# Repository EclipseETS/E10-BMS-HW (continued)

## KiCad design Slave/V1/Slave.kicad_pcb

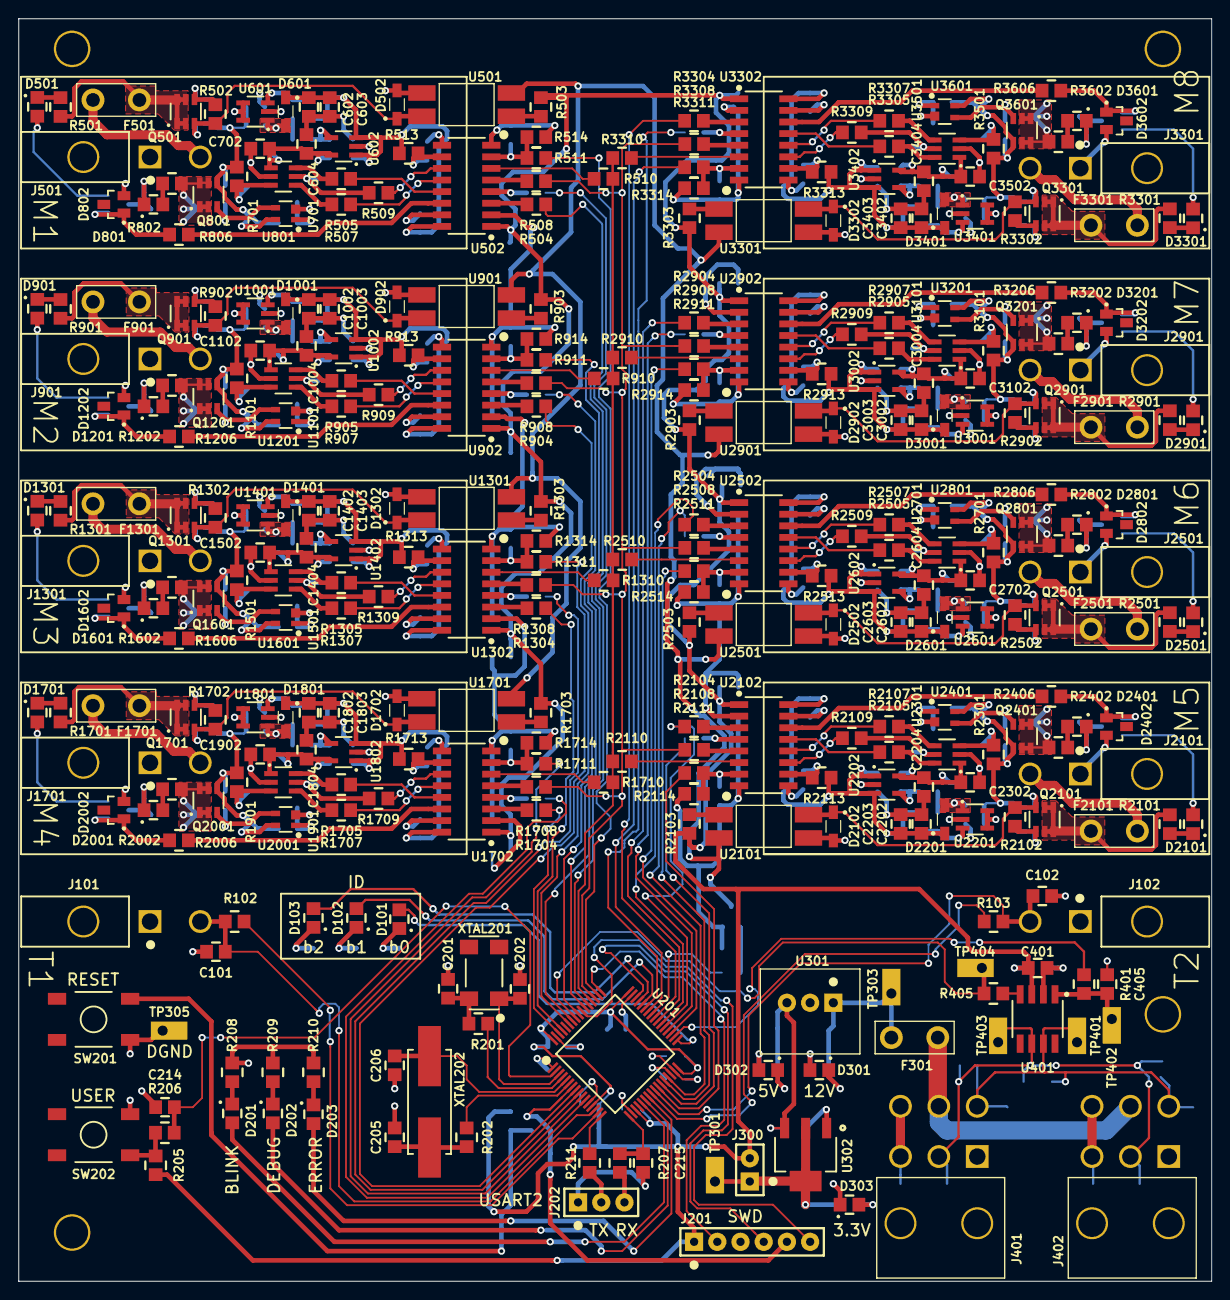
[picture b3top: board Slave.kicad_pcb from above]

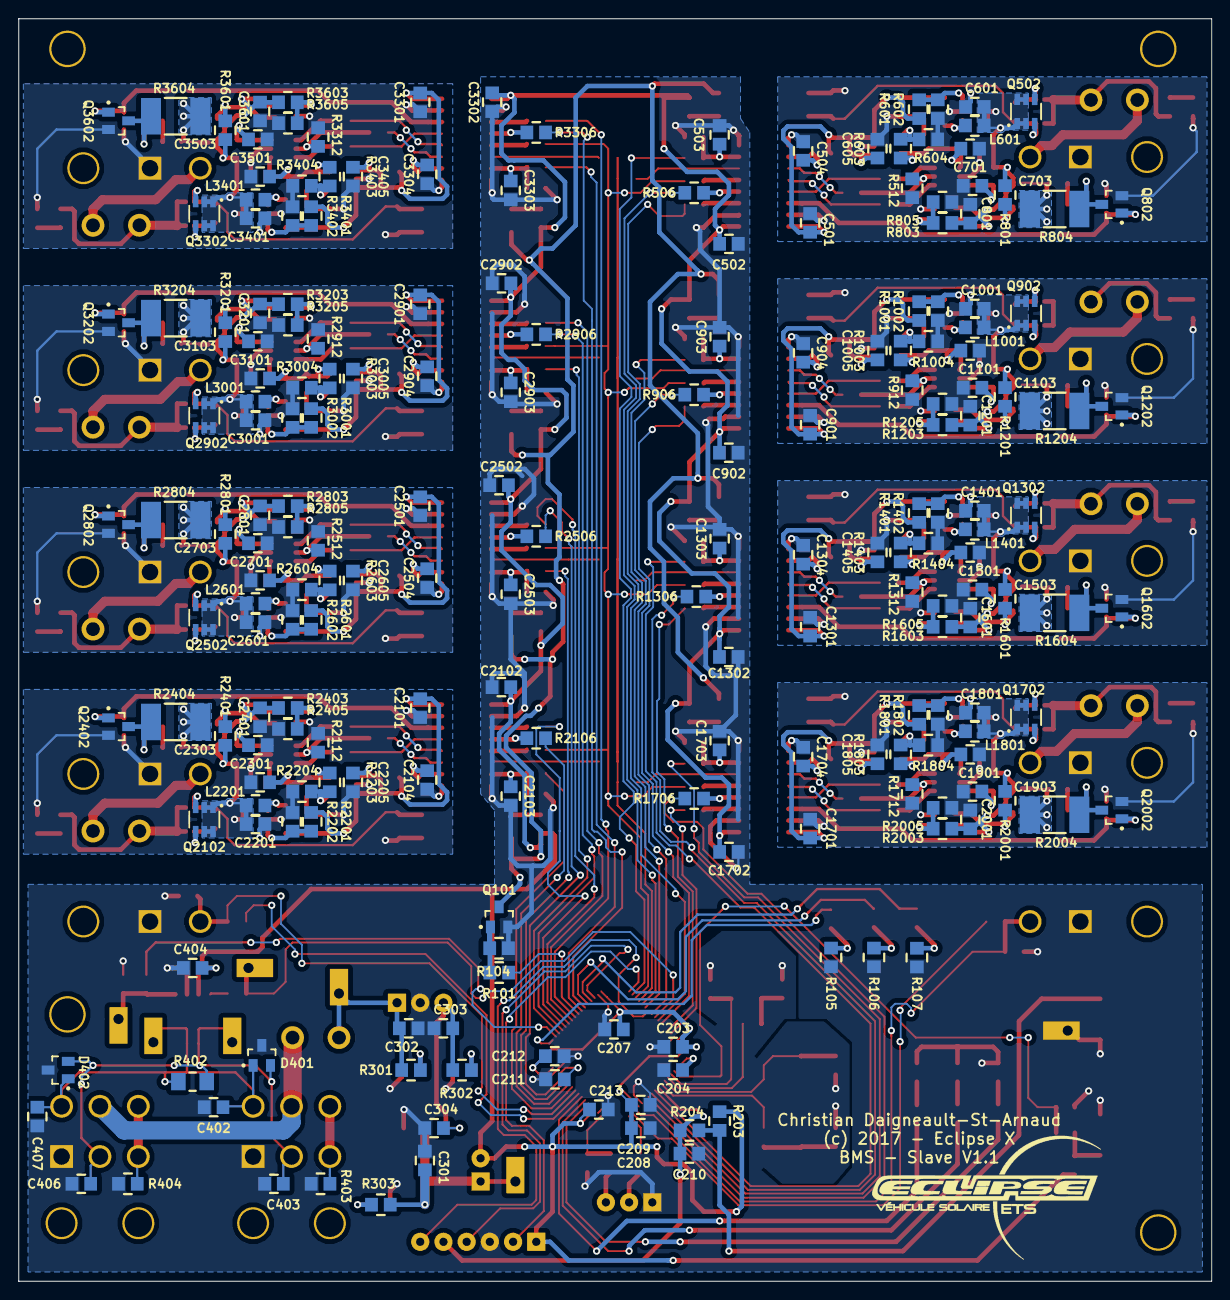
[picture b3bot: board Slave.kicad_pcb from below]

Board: 2 copper layers, 130.6 x 138.2 mm, 537 parts (210 on the bottom side), 345 nets.

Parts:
C101, C102, C204, C208, C401, C701, C1101, C1501, C1901, C2301, C2701, C3101, C3501: 885012107015; C0805
C201, C202: 885012007027; C0805
C203, C207, C210, C212, C213, C214, C404, C501, C502, C504, C702, C801, C901, C902, C904, C1102, C1201, C1301, C1302, C1304, C1502, C1601, C1701, C1702, C1704, C1902, C2001, C2101, C2102, C2104, C2302, C2401, C2501, C2502, C2504, C2702, C2801, C2901, C2902, C2904, C3102, C3201, C3301, C3302, C3304, C3502, C3601: 885012207098; C0805
C205, C206, C215, C402, C403, C406, C407: 885012007053; C0805
C209: 885012207092; C0805
C211, C302, C303: 885012107018; C0805
C301: 885012107005; C0805
C304, C601, C602, C603, C604, C605, C1001, C1002, C1003, C1004, C1005, C1401, C1402, C1403, C1404, C1405, C1801, C1802, C1803, C1804, C1805, C2201, C2202, C2203, C2204, C2205, C2601, C2602, C2603, C2604, C2605, C3001, C3002, C3003, C3004, C3005, C3401, C3402, C3403, C3404, C3405: 885012107014; C0805
C405, C503, C903, C1303, C1703, C2103, C2503, C2903, C3303: 885012207080; C0805
C703, C1103, C1503, C1903, C2303, C2703, C3103, C3503: 885012207047; C0805
D101, D102, D103, D201, D301, D302, D303, D801, D1201, D1601, D2001, D2401, D2801, D3201, D3601: 150080VS75000; LED_0805_GREEN
D202: 150080YS75000; LED_0805_YELLOW
D203, D501, D901, D1301, D1701, D2101, D2501, D2901, D3301: 150080RS75000; LED_0805_RED
D401, D402: D1213A-02SOL-7; SOT-23-3
D502, D601, D902, D1001, D1302, D1401, D1702, D1801, D2102, D2201, D2502, D2601, D2902, D3001, D3302, D3401: NSR0530HT1G; SOD-323
D802, D1202, D1602, D2002, D2402, D2802, D3202, D3602: MMBZ12VALT1G; SOT-23-3
F301, F501, F901, F1301, F1701, F2101, F2501, F2901, F3301: 39511000440; TE5_395
J101, J102, J501, J901, J1301, J1701, J2101, J2501, J2901, J3301: 649002227222
J201: Header_Male_Pin_2.54mm_1X6_,_Unshrouded; Headers_2.54mm_1X6
J202: Header_Male_Pin_2.54mm_1X3_,_Unshrouded; Headers_2.54mm_1X3
J300: Header_Male_Pin_2.54mm_1X2_,_Unshrouded; Headers_2.54mm_1X2
J401, J402: 649006227222
L601, L1001, L1401, L1801, L2201, L2601, L3001, L3401: MLZ2012N101LT000; I0805
Q101: 2N7002P,215; SOT-23-3
Q501, Q502, Q801, Q901, Q902, Q1201, Q1301, Q1302, Q1601, Q1701, Q1702, Q2001, Q2101, Q2102, Q2401, Q2501, Q2502, Q2801, Q2901, Q2902, Q3201, Q3301, Q3302, Q3601: CPH6347-TL-W; TSOT-23-6
Q802, Q1202, Q1602, Q2002, Q2402, Q2802, Q3202, Q3602: BSS806NH6327XTSA1; SOT-23-3
R101, R105, R106, R107, R208, R209, R210, R303: RC0805JR-07470RL; R0805
R102, R103: RC0805JR-0733KL; R0805
R104, R203, R205, R207, R301, R510, R511, R512, R513, R603, R910, R911, R912, R913, R1003, R1310, R1311, R1312, R1313, R1403, R1710, R1711, R1712, R1713, R1803, R2110, R2111, R2112, R2113, R2203, R2510, R2511, R2512, R2513, R2603, R2910, R2911, R2912, R2913, R3003, R3310, R3311, R3312, R3313, R3403: RC0805JR-074K7L; R0805
R201, R202, R403, R404: RC0805JR-070RL; R0805
R204, R206, R401, R405, R504, R505, R506, R507, R508, R509, R701, R904, R905, R906, R907, R908, R909, R1101, R1304, R1305, R1306, R1307, R1308, R1309, R1501, R1704, R1705, R1706, R1707, R1708, R1709, R1901, R2104, R2105, R2106, R2107, R2108, R2109, R2301, R2504, R2505, R2506, R2507, R2508, R2509, R2701, R2904, R2905, R2906, R2907, R2908, R2909, R3101, R3304, R3305, R3306, R3307, R3308, R3309, R3501: RC0805JR-07100RL; R0805
R211, R302, R501, R802, R901, R1202, R1301, R1602, R1701, R2002, R2101, R2402, R2501, R2802, R2901, R3202, R3301, R3602: RC0805JR-071KL; R0805
R402: RC1206JR-07120RL; R1206
R502, R514, R801, R902, R914, R1201, R1302, R1314, R1601, R1702, R1714, R2001, R2102, R2114, R2401, R2502, R2514, R2801, R2902, R2914, R3201, R3302, R3314, R3601: RC0805JR-07470KL; R0805
R503, R903, R1303, R1703, R2103, R2503, R2903, R3303: RC0805JR-07330RL; R0805
R601, R1001, R1401, R1801, R2201, R2601, R3001, R3401: RC0805JR-071ML; R0805
R602, R1002, R1402, R1802, R2202, R2602, R3002, R3402: RC0805FR-07324KL; R0805
R604, R1004, R1404, R1804, R2204, R2604, R3004, R3404: RC0805FR-0712K1L; R0805
R803, R1203, R1603, R2003, R2403, R2803, R3203, R3603: RC0805JR-07560KL; R0805
R804, R1204, R1604, R2004, R2404, R2804, R3204, R3604: 352210RJT; R2512
R805, R1205, R1605, R2005, R2405, R2805, R3205, R3605: RC0805JR-07100KL; R0805
R806, R1206, R1606, R2006, R2406, R2806, R3206, R3606: RC0805JR-076K8L; R0805
SW201, SW202: PTS645SM43SMTR92; PTS645_6X6X4_SMD
TP301, TP303, TP305, TP401, TP402, TP403, TP404: Test_Point_THM; Keystone_5001
U201: STM32F446RE; LQFP-64
U301: OKI-78SR-5/1.5-W36-C; OKI-78SR_Vertical
U302: AZ1117IH-3.3TRG1; SOT-223-3
U401: SN65HVD232DR; SOIC-8
U501, U901, U1301, U1701, U2101, U2501, U2901, U3301: LTV-816S; 4-SMD
U502, U902, U1302, U1702, U2102, U2502, U2902, U3302: SI8641AB-B-IS1; SOIC-16
U601, U1001, U1401, U1801, U2201, U2601, U3001, U3401: AP3015KTR-G1; SOT-23-5
U602, U1002, U1402, U1802, U2202, U2602, U3002, U3402: AP2202K-ADJTRG1; SOT-23-5
U701, U1101, U1501, U1901, U2301, U2701, U3101, U3501: ADC121S021CIMF/NOPB; SOT-23-6
U801, U1201, U1601, U2001, U2401, U2801, U3201, U3601: ADCMP350YKSZ-REEL7; SC70-4
XTAL201: ABS25-32.768KHZ-6-T; ABS25
XTAL202: ABLS-8.000MHZ-D-T; HC49_US

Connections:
3.3V: C301.2, J300.1, R303.2, TP301.1, U302.2, U302.4
5V: C303.2, C304.2, R302.2, U301.3, U302.3
12V: C302.2, F301.2, R301.2, TP303.1, U301.1
/BALANCING_PWM_1: R504.2, U201.58
/BALANCING_PWM_2: R904.2, U201.59
/BALANCING_PWM_3: R1304.2, U201.61
/BALANCING_PWM_4: R1704.2, U201.62
/BALANCING_PWM_5: R2104.2, U201.37
/BALANCING_PWM_6: R2504.2, U201.38
/BALANCING_PWM_7: R2904.2, U201.39
/BALANCING_PWM_8: R3304.2, U201.40
/CAN1/CAN_N: C403.2, C406.2, D401.2, D402.2, J401.2, J402.2, R402.2, TP403.1, U401.6
/CAN1/CAN_P: C402.2, C407.2, D401.1, D402.1, J401.4, J402.4, R402.1, TP401.1, U401.7
/CAN1/Shield1: J401.3, J401.6, R403.1
/CAN1/Shield2: J402.3, J402.6, R404.1
/CAN2_RX: R405.1, TP404.1, U201.57
/CAN2_TX: R401.1, U201.34
/CS_1: R506.2, U201.53
/CS_2: R906.2, U201.56
/CS_3: R1306.2, U201.9
/CS_4: R1706.2, U201.11
/CS_5: R2106.2, U201.27
/CS_6: R2506.2, U201.29
/CS_7: R2906.2, U201.36
/CS_8: R3306.2, U201.43
/DATA_ENABLE_1: R511.2, U201.50
/DATA_ENABLE_2: R911.2, U201.54
/DATA_ENABLE_3: R1311.2, U201.8
/DATA_ENABLE_4: R1711.2, U201.10
/DATA_ENABLE_5: R2111.2, U201.26
/DATA_ENABLE_6: R2511.2, U201.28
/DATA_ENABLE_7: R2911.2, U201.35
/DATA_ENABLE_8: R3311.2, U201.42
/ID_0: D101.2, U201.33
/ID_1: D102.2, U201.44
/ID_2: D103.2, U201.45
/MISO: R510.2, R910.2, R1310.2, R1710.2, R2110.2, R2510.2, R2910.2, R3310.2, U201.52
/Module 1/+VREF: C604.2, C701.1, C702.1, R603.2, U602.5, U701.1
/Module 1/BALANCE_PWM: R806.1, U502.14
/Module 1/BVDD: C501.2, C602.2, C603.2, C605.2, D601.1, R513.2, R601.2, U502.16, U602.1, U602.3
/Module 1/Balancing/Drain_P_Mosfet: Q801.1, Q801.2, Q801.5, Q801.6, R802.1, R804.2
/Module 1/CELL+: F501.2, Q501.1, Q501.2, Q501.5, Q501.6, R501.2
/Module 1/CELL-: C501.1, C504.1, C601.1, C602.1, C603.1, C604.1, C605.1, C701.2, C702.2, C703.1, C801.2, D501.2, D502.2, D802.2, J501.1, Q802.2, R512.1, R602.1, R604.1, R805.1, U501.3, U502.9, U502.15, U601.2, U602.2, U701.2, U801.2
/Module 1/CELL_Voltage: C601.2, C801.1, L601.1, Q502.1, Q502.2, Q502.5, Q502.6, Q801.4, R701.1, R801.1, R803.2, U601.4, U601.5, U801.4
/Module 1/CS: R505.2, U502.13
/Module 1/Power Supply Front End/SW: D601.2, L601.2, U601.1
/Module 1/SCLK: R507.2, U502.12
/Module 1/SDATA: R509.2, U502.11
/Module 1/Voltage Reading/CS: R505.1, U701.6
/Module 1/Voltage Reading/SCLK: R507.1, U701.4
/Module 1/Voltage Reading/SDATA: R509.1, R512.2, U701.5
/Module 2/+VREF: C1004.2, C1101.1, C1102.1, R1003.2, U1002.5, U1101.1
/Module 2/BALANCE_PWM: R1206.1, U902.14
/Module 2/BVDD: C901.2, C1002.2, C1003.2, C1005.2, D1001.1, R913.2, R1001.2, U902.16, U1002.1, U1002.3
/Module 2/Balancing/Drain_P_Mosfet: Q1201.1, Q1201.2, Q1201.5, Q1201.6, R1202.1, R1204.2
/Module 2/CELL+: F901.2, Q901.1, Q901.2, Q901.5, Q901.6, R901.2
/Module 2/CELL-: C901.1, C904.1, C1001.1, C1002.1, C1003.1, C1004.1, C1005.1, C1101.2, C1102.2, C1103.1, C1201.2, D901.2, D902.2, D1202.2, J901.1, Q1202.2, R912.1, R1002.1, R1004.1, R1205.1, U901.3, U902.9, U902.15, U1001.2, U1002.2, U1101.2, U1201.2
/Module 2/CELL_Voltage: C1001.2, C1201.1, L1001.1, Q902.1, Q902.2, Q902.5, Q902.6, Q1201.4, R1101.1, R1201.1, R1203.2, U1001.4, U1001.5, U1201.4
/Module 2/CS: R905.2, U902.13
/Module 2/Power Supply Front End/SW: D1001.2, L1001.2, U1001.1
/Module 2/SCLK: R907.2, U902.12
/Module 2/SDATA: R909.2, U902.11
/Module 2/Voltage Reading/CS: R905.1, U1101.6
/Module 2/Voltage Reading/SCLK: R907.1, U1101.4
/Module 2/Voltage Reading/SDATA: R909.1, R912.2, U1101.5
/Module 3/+VREF: C1404.2, C1501.1, C1502.1, R1403.2, U1402.5, U1501.1
/Module 3/BALANCE_PWM: R1606.1, U1302.14
/Module 3/BVDD: C1301.2, C1402.2, C1403.2, C1405.2, D1401.1, R1313.2, R1401.2, U1302.16, U1402.1, U1402.3
/Module 3/Balancing/Drain_P_Mosfet: Q1601.1, Q1601.2, Q1601.5, Q1601.6, R1602.1, R1604.2
/Module 3/CELL+: F1301.2, Q1301.1, Q1301.2, Q1301.5, Q1301.6, R1301.2
/Module 3/CELL-: C1301.1, C1304.1, C1401.1, C1402.1, C1403.1, C1404.1, C1405.1, C1501.2, C1502.2, C1503.1, C1601.2, D1301.2, D1302.2, D1602.2, J1301.1, Q1602.2, R1312.1, R1402.1, R1404.1, R1605.1, U1301.3, U1302.9, U1302.15, U1401.2, U1402.2, U1501.2, U1601.2
/Module 3/CELL_Voltage: C1401.2, C1601.1, L1401.1, Q1302.1, Q1302.2, Q1302.5, Q1302.6, Q1601.4, R1501.1, R1601.1, R1603.2, U1401.4, U1401.5, U1601.4
/Module 3/CS: R1305.2, U1302.13
/Module 3/Power Supply Front End/SW: D1401.2, L1401.2, U1401.1
/Module 3/SCLK: R1307.2, U1302.12
/Module 3/SDATA: R1309.2, U1302.11
/Module 3/Voltage Reading/CS: R1305.1, U1501.6
/Module 3/Voltage Reading/SCLK: R1307.1, U1501.4
/Module 3/Voltage Reading/SDATA: R1309.1, R1312.2, U1501.5
/Module 4/+VREF: C1804.2, C1901.1, C1902.1, R1803.2, U1802.5, U1901.1
/Module 4/BALANCE_PWM: R2006.1, U1702.14
/Module 4/BVDD: C1701.2, C1802.2, C1803.2, C1805.2, D1801.1, R1713.2, R1801.2, U1702.16, U1802.1, U1802.3
/Module 4/Balancing/Drain_P_Mosfet: Q2001.1, Q2001.2, Q2001.5, Q2001.6, R2002.1, R2004.2
/Module 4/CELL+: F1701.2, Q1701.1, Q1701.2, Q1701.5, Q1701.6, R1701.2
/Module 4/CELL-: C1701.1, C1704.1, C1801.1, C1802.1, C1803.1, C1804.1, C1805.1, C1901.2, C1902.2, C1903.1, C2001.2, D1701.2, D1702.2, D2002.2, J1701.1, Q2002.2, R1712.1, R1802.1, R1804.1, R2005.1, U1701.3, U1702.9, U1702.15, U1801.2, U1802.2, U1901.2, U2001.2
/Module 4/CELL_Voltage: C1801.2, C2001.1, L1801.1, Q1702.1, Q1702.2, Q1702.5, Q1702.6, Q2001.4, R1901.1, R2001.1, R2003.2, U1801.4, U1801.5, U2001.4
/Module 4/CS: R1705.2, U1702.13
/Module 4/Power Supply Front End/SW: D1801.2, L1801.2, U1801.1
/Module 4/SCLK: R1707.2, U1702.12
/Module 4/SDATA: R1709.2, U1702.11
/Module 4/Voltage Reading/CS: R1705.1, U1901.6
/Module 4/Voltage Reading/SCLK: R1707.1, U1901.4
/Module 4/Voltage Reading/SDATA: R1709.1, R1712.2, U1901.5
/Module 5/+VREF: C2204.2, C2301.1, C2302.1, R2203.2, U2202.5, U2301.1
/Module 5/BALANCE_PWM: R2406.1, U2102.14
/Module 5/BVDD: C2101.2, C2202.2, C2203.2, C2205.2, D2201.1, R2113.2, R2201.2, U2102.16, U2202.1, U2202.3
/Module 5/Balancing/Drain_P_Mosfet: Q2401.1, Q2401.2, Q2401.5, Q2401.6, R2402.1, R2404.2
/Module 5/CELL+: F2101.2, Q2101.1, Q2101.2, Q2101.5, Q2101.6, R2101.2
/Module 5/CELL-: C2101.1, C2104.1, C2201.1, C2202.1, C2203.1, C2204.1, C2205.1, C2301.2, C2302.2, C2303.1, C2401.2, D2101.2, D2102.2, D2402.2, J2101.1, Q2402.2, R2112.1, R2202.1, R2204.1, R2405.1, U2101.3, U2102.9, U2102.15, U2201.2, U2202.2, U2301.2, U2401.2
/Module 5/CELL_Voltage: C2201.2, C2401.1, L2201.1, Q2102.1, Q2102.2, Q2102.5, Q2102.6, Q2401.4, R2301.1, R2401.1, R2403.2, U2201.4, U2201.5, U2401.4
/Module 5/CS: R2105.2, U2102.13
/Module 5/Power Supply Front End/SW: D2201.2, L2201.2, U2201.1
/Module 5/SCLK: R2107.2, U2102.12
/Module 5/SDATA: R2109.2, U2102.11
/Module 5/Voltage Reading/CS: R2105.1, U2301.6
/Module 5/Voltage Reading/SCLK: R2107.1, U2301.4
/Module 5/Voltage Reading/SDATA: R2109.1, R2112.2, U2301.5
/Module 6/+VREF: C2604.2, C2701.1, C2702.1, R2603.2, U2602.5, U2701.1
/Module 6/BALANCE_PWM: R2806.1, U2502.14
/Module 6/BVDD: C2501.2, C2602.2, C2603.2, C2605.2, D2601.1, R2513.2, R2601.2, U2502.16, U2602.1, U2602.3
/Module 6/Balancing/Drain_P_Mosfet: Q2801.1, Q2801.2, Q2801.5, Q2801.6, R2802.1, R2804.2
/Module 6/CELL+: F2501.2, Q2501.1, Q2501.2, Q2501.5, Q2501.6, R2501.2
/Module 6/CELL-: C2501.1, C2504.1, C2601.1, C2602.1, C2603.1, C2604.1, C2605.1, C2701.2, C2702.2, C2703.1, C2801.2, D2501.2, D2502.2, D2802.2, J2501.1, Q2802.2, R2512.1, R2602.1, R2604.1, R2805.1, U2501.3, U2502.9, U2502.15, U2601.2, U2602.2, U2701.2, U2801.2
/Module 6/CELL_Voltage: C2601.2, C2801.1, L2601.1, Q2502.1, Q2502.2, Q2502.5, Q2502.6, Q2801.4, R2701.1, R2801.1, R2803.2, U2601.4, U2601.5, U2801.4
/Module 6/CS: R2505.2, U2502.13
/Module 6/Power Supply Front End/SW: D2601.2, L2601.2, U2601.1
/Module 6/SCLK: R2507.2, U2502.12
/Module 6/SDATA: R2509.2, U2502.11
/Module 6/Voltage Reading/CS: R2505.1, U2701.6
/Module 6/Voltage Reading/SCLK: R2507.1, U2701.4
/Module 6/Voltage Reading/SDATA: R2509.1, R2512.2, U2701.5
/Module 7/+VREF: C3004.2, C3101.1, C3102.1, R3003.2, U3002.5, U3101.1
/Module 7/BALANCE_PWM: R3206.1, U2902.14
/Module 7/BVDD: C2901.2, C3002.2, C3003.2, C3005.2, D3001.1, R2913.2, R3001.2, U2902.16, U3002.1, U3002.3
/Module 7/Balancing/Drain_P_Mosfet: Q3201.1, Q3201.2, Q3201.5, Q3201.6, R3202.1, R3204.2
/Module 7/CELL+: F2901.2, Q2901.1, Q2901.2, Q2901.5, Q2901.6, R2901.2
/Module 7/CELL-: C2901.1, C2904.1, C3001.1, C3002.1, C3003.1, C3004.1, C3005.1, C3101.2, C3102.2, C3103.1, C3201.2, D2901.2, D2902.2, D3202.2, J2901.1, Q3202.2, R2912.1, R3002.1, R3004.1, R3205.1, U2901.3, U2902.9, U2902.15, U3001.2, U3002.2, U3101.2, U3201.2
/Module 7/CELL_Voltage: C3001.2, C3201.1, L3001.1, Q2902.1, Q2902.2, Q2902.5, Q2902.6, Q3201.4, R3101.1, R3201.1, R3203.2, U3001.4, U3001.5, U3201.4
/Module 7/CS: R2905.2, U2902.13
/Module 7/Power Supply Front End/SW: D3001.2, L3001.2, U3001.1
/Module 7/SCLK: R2907.2, U2902.12
/Module 7/SDATA: R2909.2, U2902.11
/Module 7/Voltage Reading/CS: R2905.1, U3101.6
/Module 7/Voltage Reading/SCLK: R2907.1, U3101.4
/Module 7/Voltage Reading/SDATA: R2909.1, R2912.2, U3101.5
/Module 8/+VREF: C3404.2, C3501.1, C3502.1, R3403.2, U3402.5, U3501.1
/Module 8/BALANCE_PWM: R3606.1, U3302.14
/Module 8/BVDD: C3301.2, C3402.2, C3403.2, C3405.2, D3401.1, R3313.2, R3401.2, U3302.16, U3402.1, U3402.3
/Module 8/Balancing/Drain_P_Mosfet: Q3601.1, Q3601.2, Q3601.5, Q3601.6, R3602.1, R3604.2
/Module 8/CELL+: F3301.2, Q3301.1, Q3301.2, Q3301.5, Q3301.6, R3301.2
/Module 8/CELL-: C3301.1, C3304.1, C3401.1, C3402.1, C3403.1, C3404.1, C3405.1, C3501.2, C3502.2, C3503.1, C3601.2, D3301.2, D3302.2, D3602.2, J3301.1, Q3602.2, R3312.1, R3402.1, R3404.1, R3605.1, U3301.3, U3302.9, U3302.15, U3401.2, U3402.2, U3501.2, U3601.2
/Module 8/CELL_Voltage: C3401.2, C3601.1, L3401.1, Q3302.1, Q3302.2, Q3302.5, Q3302.6, Q3601.4, R3501.1, R3601.1, R3603.2, U3401.4, U3401.5, U3601.4
/Module 8/CS: R3305.2, U3302.13
/Module 8/Power Supply Front End/SW: D3401.2, L3401.2, U3401.1
/Module 8/SCLK: R3307.2, U3302.12
/Module 8/SDATA: R3309.2, U3302.11
/Module 8/Voltage Reading/CS: R3305.1, U3501.6
/Module 8/Voltage Reading/SCLK: R3307.1, U3501.4
/Module 8/Voltage Reading/SDATA: R3309.1, R3312.2, U3501.5
/NRST: C210.1, J201.5, R204.2, U201.7
/NTC_1_ADC: C101.2, J101.2, R102.1, U201.14
/NTC_1_GPIO: R102.2, U201.15
/NTC_2_ADC: C102.2, J102.2, R103.1, U201.25
/NTC_2_GPIO: R103.2, U201.24
/PA5: D201.2, U201.21
/PA6: D202.2, U201.22
/PA7: D203.2, U201.23
/PWR_ENABLE: Q101.3, U501.2, U901.2, U1301.2, U1701.2, U2101.2, U2501.2, U2901.2, U3301.2
/PWR_ENABLE_GPIO: R101.2, U201.41
/SCLK: R508.2, R908.2, R1308.2, R1708.2, R2108.2, R2508.2, R2908.2, R3308.2, U201.51
/STM32F446/PA2: R211.2, U201.16
/STM32F446/PA3: C215.2, R207.2, U201.17
/STM32F446/SWCLK: J201.2, U201.49
/STM32F446/SWDIO: J201.4, U201.46
/STM32F446/SWO: J201.6, U201.55
/STM32F446/USART2_RX: J202.3, R207.1
/STM32F446/USART2_TX: J202.2, R211.1
/STM32F446/USER_BTN: C214.1, R206.2, U201.2
/VBat: C204.2, U201.1
CAN_PWR: F301.1, J401.5, J402.5
DGND: C101.1, C102.1, C201.1, C202.2, C203.1, C204.1, C205.1, C206.2, C207.2, C208.1, C209.1, C210.2, C211.1, C212.2, C213.2, C214.2, C215.1, C301.1, C302.1, C303.1, C304.1, C401.1, C402.1, C403.1, C404.1, C405.1, C406.1, C407.1, C502.2, C503.1, C902.2, C903.1, C1302.2, C1303.1, C1702.2, C1703.1, C2102.2, C2103.1, C2502.2, C2503.1, C2902.2, C2903.1, C3302.2, C3303.1, D301.1, D302.1, D303.1, D401.3, D402.3, J101.1, J102.1, J201.3, J202.1, J401.1, J402.1, Q101.2, R104.1, R105.1, R106.1, R107.1, R208.1, R209.1, R210.1, R403.2, R404.2, R514.1, R914.1, R1314.1, R1714.1, R2114.1, R2514.1, R2914.1, R3314.1, SW201.4, SW202.3, TP305.1, U201.12, U201.18, U201.31, U201.47, U201.63, U301.2, U302.1, U401.2, U502.2, U502.8, U902.2, U902.8, U1302.2, U1302.8, U1702.2, U1702.8, U2102.2, U2102.8, U2502.2, U2502.8, U2902.2, U2902.8, U3302.2, U3302.8
unnamed: C201.2, R201.2, XTAL201.4
unnamed: C202.1, U201.3, XTAL201.1
unnamed: C205.2, R202.2, XTAL202.1
unnamed: C206.1, U201.5, XTAL202.2
unnamed: C211.2, U201.30
unnamed: C405.2, R401.2, TP402.1, U401.1
unnamed: C503.2, R511.1, R514.2, U502.7
unnamed: C504.2, R513.1, U502.10
unnamed: C703.2, R701.2, U701.3
unnamed: C903.2, R911.1, R914.2, U902.7
unnamed: C904.2, R913.1, U902.10
unnamed: C1103.2, R1101.2, U1101.3
unnamed: C1303.2, R1311.1, R1314.2, U1302.7
unnamed: C1304.2, R1313.1, U1302.10
unnamed: C1503.2, R1501.2, U1501.3
unnamed: C1703.2, R1711.1, R1714.2, U1702.7
unnamed: C1704.2, R1713.1, U1702.10
unnamed: C1903.2, R1901.2, U1901.3
unnamed: C2103.2, R2111.1, R2114.2, U2102.7
unnamed: C2104.2, R2113.1, U2102.10
unnamed: C2303.2, R2301.2, U2301.3
unnamed: C2503.2, R2511.1, R2514.2, U2502.7
unnamed: C2504.2, R2513.1, U2502.10
unnamed: C2703.2, R2701.2, U2701.3
unnamed: C2903.2, R2911.1, R2914.2, U2902.7
unnamed: C2904.2, R2913.1, U2902.10
unnamed: C3103.2, R3101.2, U3101.3
unnamed: C3303.2, R3311.1, R3314.2, U3302.7
unnamed: C3304.2, R3313.1, U3302.10
unnamed: C3503.2, R3501.2, U3501.3
unnamed: D101.1, R105.2
unnamed: D102.1, R106.2
unnamed: D103.1, R107.2
unnamed: D201.1, R208.2
unnamed: D202.1, R209.2
unnamed: D203.1, R210.2
unnamed: D301.2, R301.1
unnamed: D302.2, R302.1
unnamed: D303.2, R303.1
unnamed: D501.1, R501.1
unnamed: D502.1, Q501.3, Q502.3, R502.1, U501.4
unnamed: D801.1, Q802.3, R804.1
unnamed: D801.2, R802.2
unnamed: D802.1, Q802.1, R806.2
unnamed: D901.1, R901.1
unnamed: D902.1, Q901.3, Q902.3, R902.1, U901.4
unnamed: D1201.1, Q1202.3, R1204.1
unnamed: D1201.2, R1202.2
unnamed: D1202.1, Q1202.1, R1206.2
unnamed: D1301.1, R1301.1
unnamed: D1302.1, Q1301.3, Q1302.3, R1302.1, U1301.4
unnamed: D1601.1, Q1602.3, R1604.1
unnamed: D1601.2, R1602.2
unnamed: D1602.1, Q1602.1, R1606.2
unnamed: D1701.1, R1701.1
unnamed: D1702.1, Q1701.3, Q1702.3, R1702.1, U1701.4
unnamed: D2001.1, Q2002.3, R2004.1
unnamed: D2001.2, R2002.2
unnamed: D2002.1, Q2002.1, R2006.2
unnamed: D2101.1, R2101.1
unnamed: D2102.1, Q2101.3, Q2102.3, R2102.1, U2101.4
unnamed: D2401.1, Q2402.3, R2404.1
unnamed: D2401.2, R2402.2
unnamed: D2402.1, Q2402.1, R2406.2
unnamed: D2501.1, R2501.1
unnamed: D2502.1, Q2501.3, Q2502.3, R2502.1, U2501.4
unnamed: D2801.1, Q2802.3, R2804.1
unnamed: D2801.2, R2802.2
unnamed: D2802.1, Q2802.1, R2806.2
unnamed: D2901.1, R2901.1
unnamed: D2902.1, Q2901.3, Q2902.3, R2902.1, U2901.4
unnamed: D3201.1, Q3202.3, R3204.1
unnamed: D3201.2, R3202.2
unnamed: D3202.1, Q3202.1, R3206.2
unnamed: D3301.1, R3301.1
unnamed: D3302.1, Q3301.3, Q3302.3, R3302.1, U3301.4
unnamed: D3601.1, Q3602.3, R3604.1
unnamed: D3601.2, R3602.2
unnamed: D3602.1, Q3602.1, R3606.2
unnamed: F501.1, J501.2
unnamed: F901.1, J901.2
unnamed: F1301.1, J1301.2
unnamed: F1701.1, J1701.2
unnamed: F2101.1, J2101.2
unnamed: F2501.1, J2501.2
unnamed: F2901.1, J2901.2
unnamed: F3301.1, J3301.2
unnamed: Q101.1, R101.1, R104.2
unnamed: Q501.4, Q502.4, R502.2
unnamed: Q801.3, R801.2, U801.3
unnamed: Q901.4, Q902.4, R902.2
unnamed: Q1201.3, R1201.2, U1201.3
unnamed: Q1301.4, Q1302.4, R1302.2
unnamed: Q1601.3, R1601.2, U1601.3
unnamed: Q1701.4, Q1702.4, R1702.2
unnamed: Q2001.3, R2001.2, U2001.3
unnamed: Q2101.4, Q2102.4, R2102.2
unnamed: Q2401.3, R2401.2, U2401.3
unnamed: Q2501.4, Q2502.4, R2502.2
unnamed: Q2801.3, R2801.2, U2801.3
unnamed: Q2901.4, Q2902.4, R2902.2
unnamed: Q3201.3, R3201.2, U3201.3
unnamed: Q3301.4, Q3302.4, R3302.2
unnamed: Q3601.3, R3601.2, U3601.3
unnamed: R201.1, U201.4
unnamed: R202.1, U201.6
unnamed: R203.1, R204.1, SW201.2
unnamed: R205.1, R206.1, SW202.1
unnamed: R405.2, U401.4
unnamed: R503.1, U501.1
unnamed: R504.1, U502.3
unnamed: R506.1, U502.4
unnamed: R508.1, U502.5
unnamed: R510.1, U502.6
unnamed: R601.1, R602.2, U601.3
unnamed: R603.1, R604.2, U602.4
unnamed: R803.1, R805.2, U801.1
unnamed: R903.1, U901.1
unnamed: R904.1, U902.3
unnamed: R906.1, U902.4
unnamed: R908.1, U902.5
unnamed: R910.1, U902.6
unnamed: R1001.1, R1002.2, U1001.3
unnamed: R1003.1, R1004.2, U1002.4
unnamed: R1203.1, R1205.2, U1201.1
unnamed: R1303.1, U1301.1
unnamed: R1304.1, U1302.3
unnamed: R1306.1, U1302.4
unnamed: R1308.1, U1302.5
unnamed: R1310.1, U1302.6
unnamed: R1401.1, R1402.2, U1401.3
unnamed: R1403.1, R1404.2, U1402.4
unnamed: R1603.1, R1605.2, U1601.1
unnamed: R1703.1, U1701.1
unnamed: R1704.1, U1702.3
unnamed: R1706.1, U1702.4
unnamed: R1708.1, U1702.5
unnamed: R1710.1, U1702.6
unnamed: R1801.1, R1802.2, U1801.3
unnamed: R1803.1, R1804.2, U1802.4
unnamed: R2003.1, R2005.2, U2001.1
unnamed: R2103.1, U2101.1
unnamed: R2104.1, U2102.3
unnamed: R2106.1, U2102.4
unnamed: R2108.1, U2102.5
unnamed: R2110.1, U2102.6
unnamed: R2201.1, R2202.2, U2201.3
unnamed: R2203.1, R2204.2, U2202.4
unnamed: R2403.1, R2405.2, U2401.1
unnamed: R2503.1, U2501.1
unnamed: R2504.1, U2502.3
unnamed: R2506.1, U2502.4
unnamed: R2508.1, U2502.5
unnamed: R2510.1, U2502.6
unnamed: R2601.1, R2602.2, U2601.3
unnamed: R2603.1, R2604.2, U2602.4
unnamed: R2803.1, R2805.2, U2801.1
unnamed: R2903.1, U2901.1
unnamed: R2904.1, U2902.3
unnamed: R2906.1, U2902.4
unnamed: R2908.1, U2902.5
unnamed: R2910.1, U2902.6
unnamed: R3001.1, R3002.2, U3001.3
unnamed: R3003.1, R3004.2, U3002.4
unnamed: R3203.1, R3205.2, U3201.1
unnamed: R3303.1, U3301.1
unnamed: R3304.1, U3302.3
unnamed: R3306.1, U3302.4
unnamed: R3308.1, U3302.5
unnamed: R3310.1, U3302.6
unnamed: R3401.1, R3402.2, U3401.3
unnamed: R3403.1, R3404.2, U3402.4
unnamed: R3603.1, R3605.2, U3601.1
VDD: C203.2, C207.1, C208.2, C209.2, C212.1, C213.1, C401.2, C404.2, C502.1, C902.1, C1302.1, C1702.1, C2102.1, C2502.1, C2902.1, C3302.1, J201.1, J300.2, R203.2, R205.2, R503.2, R903.2, R1303.2, R1703.2, R2103.2, R2503.2, R2903.2, R3303.2, U201.13, U201.19, U201.32, U201.48, U201.64, U401.3, U502.1, U902.1, U1302.1, U1702.1, U2102.1, U2502.1, U2902.1, U3302.1

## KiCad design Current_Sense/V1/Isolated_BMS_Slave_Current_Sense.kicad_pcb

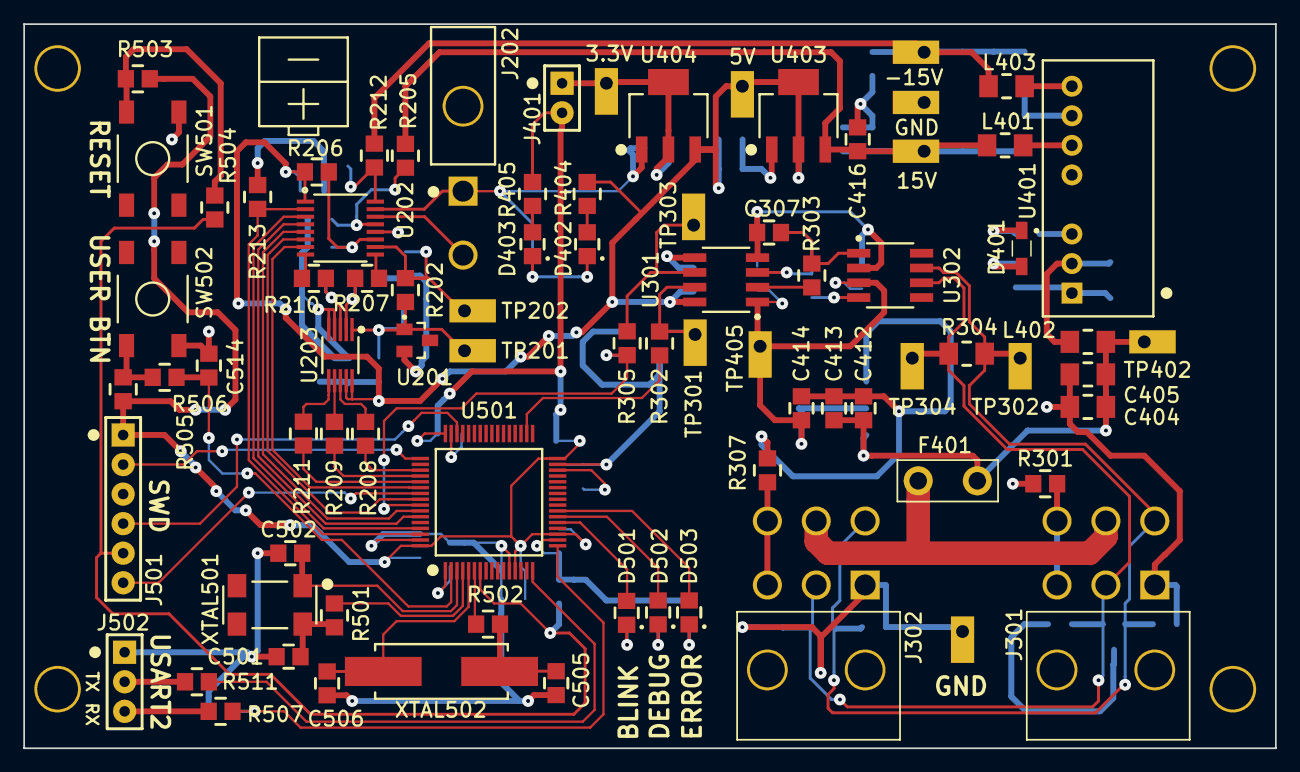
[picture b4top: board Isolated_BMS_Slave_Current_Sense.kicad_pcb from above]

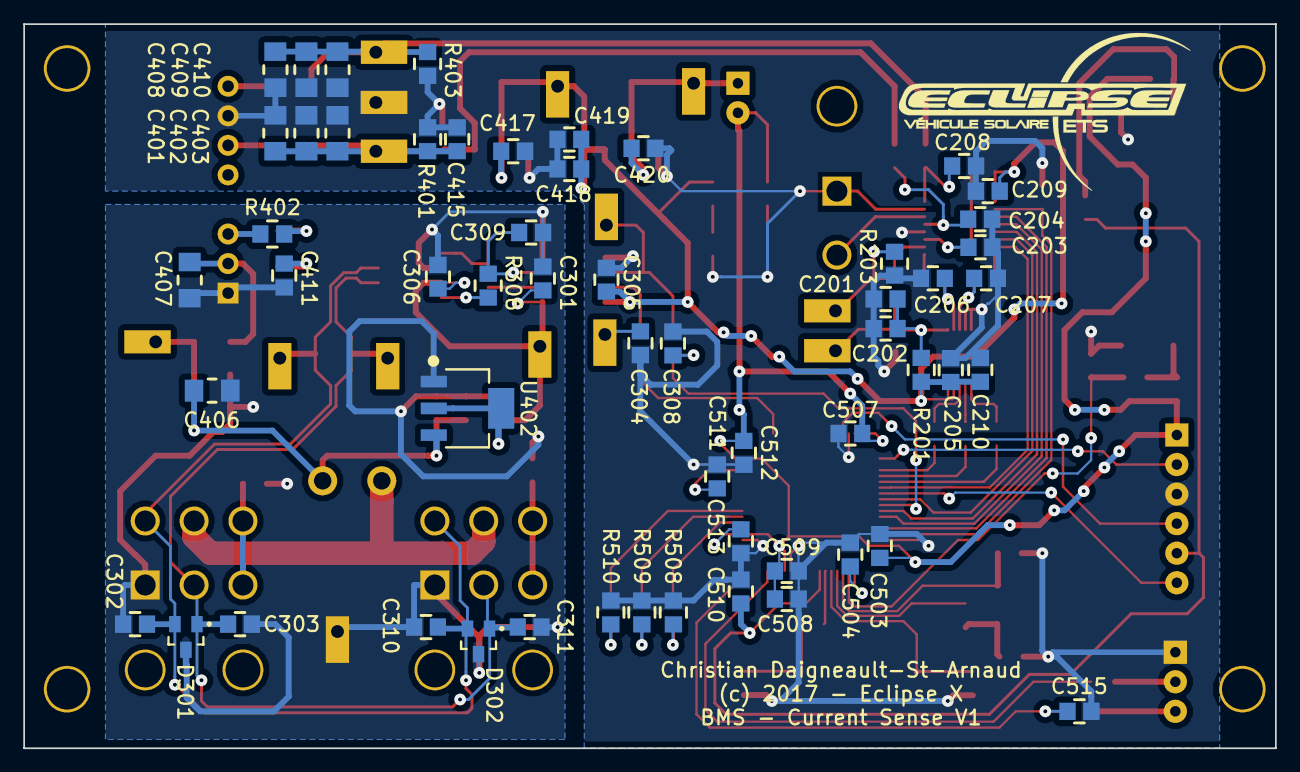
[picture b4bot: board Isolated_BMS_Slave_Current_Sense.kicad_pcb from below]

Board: 2 copper layers, 107.6 x 62.2 mm, 137 parts (56 on the bottom side), 77 nets.

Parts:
C201, C504, C508: 885012107015; C0805
C202, C205, C209, C301, C305, C306, C411, C503, C507, C510, C512, C513, C514: 885012207098; C0805
C203, C204, C208: 885012207102; C0805
C206, C207, C302, C303, C310, C311: Capacitor_Generic; C0805
C210, C412, C413, C415, C416, C418, C419, C511: 885012107018; C0805
C304, C307, C308, C309: 885012207080; C0805
C401, C402, C403, C404, C405, C406, C407, C408, C409, C410: C3216X5R1E336M160AC; C1206
C414, C417, C420: 885012107014; C0805
C501, C502: 885012007027; C0805
C505, C506, C515: 885012007053; C0805
C509: 885012207092; C0805
D301, D302: D1213A-02SOL-7; SOT-23-3
D401: NSR0530HT1G; SOD-323
D402, D403, D501: 150080VS75000; LED_0805_GREEN
D502: 150080YS75000; LED_0805_YELLOW
D503: 150080RS75000; LED_0805_RED
F401: 39511000440; TE5_395
J202: 649002227222
J301, J302: 649006227222
J401: Header_Male_Pin_2.54mm_1X2_,_Unshrouded; Headers_2.54mm_1X2
J501: Header_Male_Pin_2.54mm_1X6_,_Unshrouded; Headers_2.54mm_1X6
J502: Header_Male_Pin_2.54mm_1X3_,_Unshrouded; Headers_2.54mm_1X3
L401, L402, L403: LQM31PN4R7M00L; I1206
R201: RC0805JR-072K2L; R0805
R202, R203, R213: RC0805JR-0747KL; R0805
R205, R206, R212: RC0805JR-0722RL; R0805
R207, R210, R401, R403: Resistor_Generic; R0805
R208, R209, R211, R302, R303, R305, R306, R504, R506: RC0805JR-07100RL; R0805
R301, R307, R501, R502: RC0805JR-070RL; R0805
R304: RC1206JR-07120RL; R1206
R402, R511: RC0805JR-071KL; R0805
R404, R405, R508, R509, R510: RC0805JR-07470RL; R0805
R503, R505, R507: RC0805JR-074K7L; R0805
SW501, SW502: PTS645SM43SMTR92; PTS645_6X6X4_SMD
TP201, TP202, TP301, TP302, TP303, TP304, TP401, TP402, TP403, TP404, TP405, TP406, TP407, TP408: Test_Point_THM; Keystone_5001
U201: LM4040CYM3-4.1-TR; SOT-23-3
U202: PGA281AIPWR; TSSOP-16
U203: ADC141S626CIMM/NOPB; VSSOP-10
U301: SI8422AB-D-IS; SOIC-8
U302: SN65HVD232DR; SOIC-8
U401: PQMC3-D12-D15-S; PQMC3
U402, U404: NCP1117LPST33T3G; SOT-223-3
U403: NCP1117ST50T3G; SOT-223-3
U501: STM32F446RE; LQFP-64
XTAL501: ABS25-32.768KHZ-6-T; ABS25
XTAL502: ABLS-8.000MHZ-D-T; HC49_US

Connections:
3.3VA: C301.1, C306.1, C414.2, TP405.1, U301.1, U302.3, U402.2, U402.4
5VB: C205.1, C209.1, C210.1, C305.1, C417.2, C418.2, C419.2, R201.2, R206.2, R404.2, TP406.1, U202.1, U203.9, U203.10, U301.8, U403.2, U403.4, U404.3
12VA: C404.2, C405.2, C406.2, C412.2, C413.2, F401.2, L402.2, TP402.1, U402.3
15VB: C401.2, C402.2, C403.2, C415.2, C416.2, L401.1, R205.2, R401.2, TP401.1, U403.3
-15VB: C408.1, C409.1, C410.1, L403.1, R212.1, R403.1, TP408.1
/Communication Interface/CAN_N: C303.2, C311.2, D301.1, D302.1, J301.2, J302.2, R304.1, TP304.1, U302.6
/Communication Interface/CAN_P: C302.2, C310.2, D301.2, D302.2, J301.4, J302.4, R304.2, TP302.1, U302.7
/Communication Interface/RXD: R306.2, U302.4
/Communication Interface/Shield1: J301.3, J301.6, R301.1
/Communication Interface/Shield2: J302.3, J302.6, R307.1
/Communication Interface/TXD: C307.2, R303.2, U302.1
/Communication Interface/uC_CAN_RX: R305.1, TP303.1, U301.6
/Communication Interface/uC_CAN_TX: C304.1, R302.2, TP301.1, U301.7
/Current Sense/CS: R211.2, U501.53
/Current Sense/DOUT: R209.2, U501.52
/Current Sense/EF: R213.2, U202.2, U501.62
/Current Sense/G0: U202.7, U501.54
/Current Sense/G1: U202.6, U501.56
/Current Sense/G2: U202.5, U501.58
/Current Sense/G3: U202.4, U501.59
/Current Sense/G4: U202.3, U501.61
/Current Sense/SHUNT+: J202.2, U202.14
/Current Sense/VREF: C201.2, C202.2, R201.1, R202.2, TP201.1, U201.1, U203.1
/Current Sense/VREF_DIV2: R202.1, R203.2, TP202.1, U202.10
/STM32F446/NRST: C510.1, J501.5, R504.2, U501.7
/STM32F446/PA2: R511.2, U501.16
/STM32F446/PA3: C515.2, R507.2, U501.17
/STM32F446/PA5: D501.2, U501.21
/STM32F446/PA6: D502.2, U501.22
/STM32F446/PA7: D503.2, U501.23
/STM32F446/PB5: C308.1, R305.2, U501.57
/STM32F446/PB13: R302.1, U501.34
/STM32F446/PC10: R208.2, U501.51
/STM32F446/SWCLK: J501.2, U501.49
/STM32F446/SWDIO: J501.4, U501.46
/STM32F446/SWO: J501.6, U501.55
/STM32F446/USART2_RX: J502.3, R507.1
/STM32F446/USART2_TX: J502.2, R511.1
/STM32F446/USER_BTN: C514.1, R506.2, U501.2
/STM32F446/VBat: C504.2, U501.1
CAN_PWR: F401.1, J301.5, J302.5
DGND: C201.1, C202.1, C203.2, C204.1, C205.2, C206.1, C207.2, C208.1, C209.2, C210.2, C304.2, C305.2, C308.2, C401.1, C402.1, C403.1, C408.2, C409.2, C410.2, C415.1, C416.1, C417.1, C418.1, C419.1, C420.1, C501.1, C502.2, C503.1, C504.1, C505.1, C506.2, C507.2, C508.1, C509.1, C510.2, C511.1, C512.2, C513.2, C514.2, C515.1, D402.1, D403.1, J202.1, J501.3, J502.1, R203.1, R213.1, R401.1, R403.2, R508.1, R509.1, R510.1, SW501.4, SW502.3, TP403.1, U201.2, U202.12, U202.15, U203.4, U203.5, U301.5, U401.7, U403.1, U404.1, U501.12, U501.18, U501.31, U501.47, U501.63
GNDA: C301.2, C302.1, C303.1, C306.2, C307.1, C309.1, C310.1, C311.1, C404.1, C405.1, C406.1, C407.1, C411.1, C412.1, C413.1, C414.1, D301.3, D302.3, J301.1, J302.1, R301.2, R307.2, TP404.1, U301.4, U302.2, U401.1, U402.1
unnamed: C203.1, R206.1, U202.11
unnamed: C204.2, R205.1, U202.13
unnamed: C206.2, R207.2, U203.2
unnamed: C207.1, R210.2, U203.3
unnamed: C208.2, R212.2, U202.16
unnamed: C309.2, R306.1, U301.3
unnamed: C407.2, L402.1, U401.2
unnamed: C411.2, D401.2
unnamed: C420.2, J401.1, TP407.1, U404.2, U404.4
unnamed: C501.2, R501.2, XTAL501.4
unnamed: C502.1, U501.3, XTAL501.1
unnamed: C505.2, R502.2, XTAL502.1
unnamed: C506.1, U501.5, XTAL502.2
unnamed: C511.2, U501.30
unnamed: D401.1, R402.2
unnamed: D402.2, R404.1
unnamed: D403.2, R405.1
unnamed: D501.1, R508.2
unnamed: D502.1, R509.2
unnamed: D503.1, R510.2
unnamed: L401.2, U401.6
unnamed: L403.2, U401.8
unnamed: R207.1, U202.9
unnamed: R208.1, U203.8
unnamed: R209.1, U203.7
unnamed: R210.1, U202.8
unnamed: R211.1, U203.6
unnamed: R303.1, U301.2
unnamed: R402.1, U401.3
unnamed: R501.1, U501.4
unnamed: R502.1, U501.6
unnamed: R503.1, R504.1, SW501.2
unnamed: R505.1, R506.1, SW502.1
VDD: C503.2, C507.1, C508.2, C509.2, C512.1, C513.1, J401.2, J501.1, R405.2, R503.2, R505.2, U501.13, U501.19, U501.32, U501.48, U501.64
